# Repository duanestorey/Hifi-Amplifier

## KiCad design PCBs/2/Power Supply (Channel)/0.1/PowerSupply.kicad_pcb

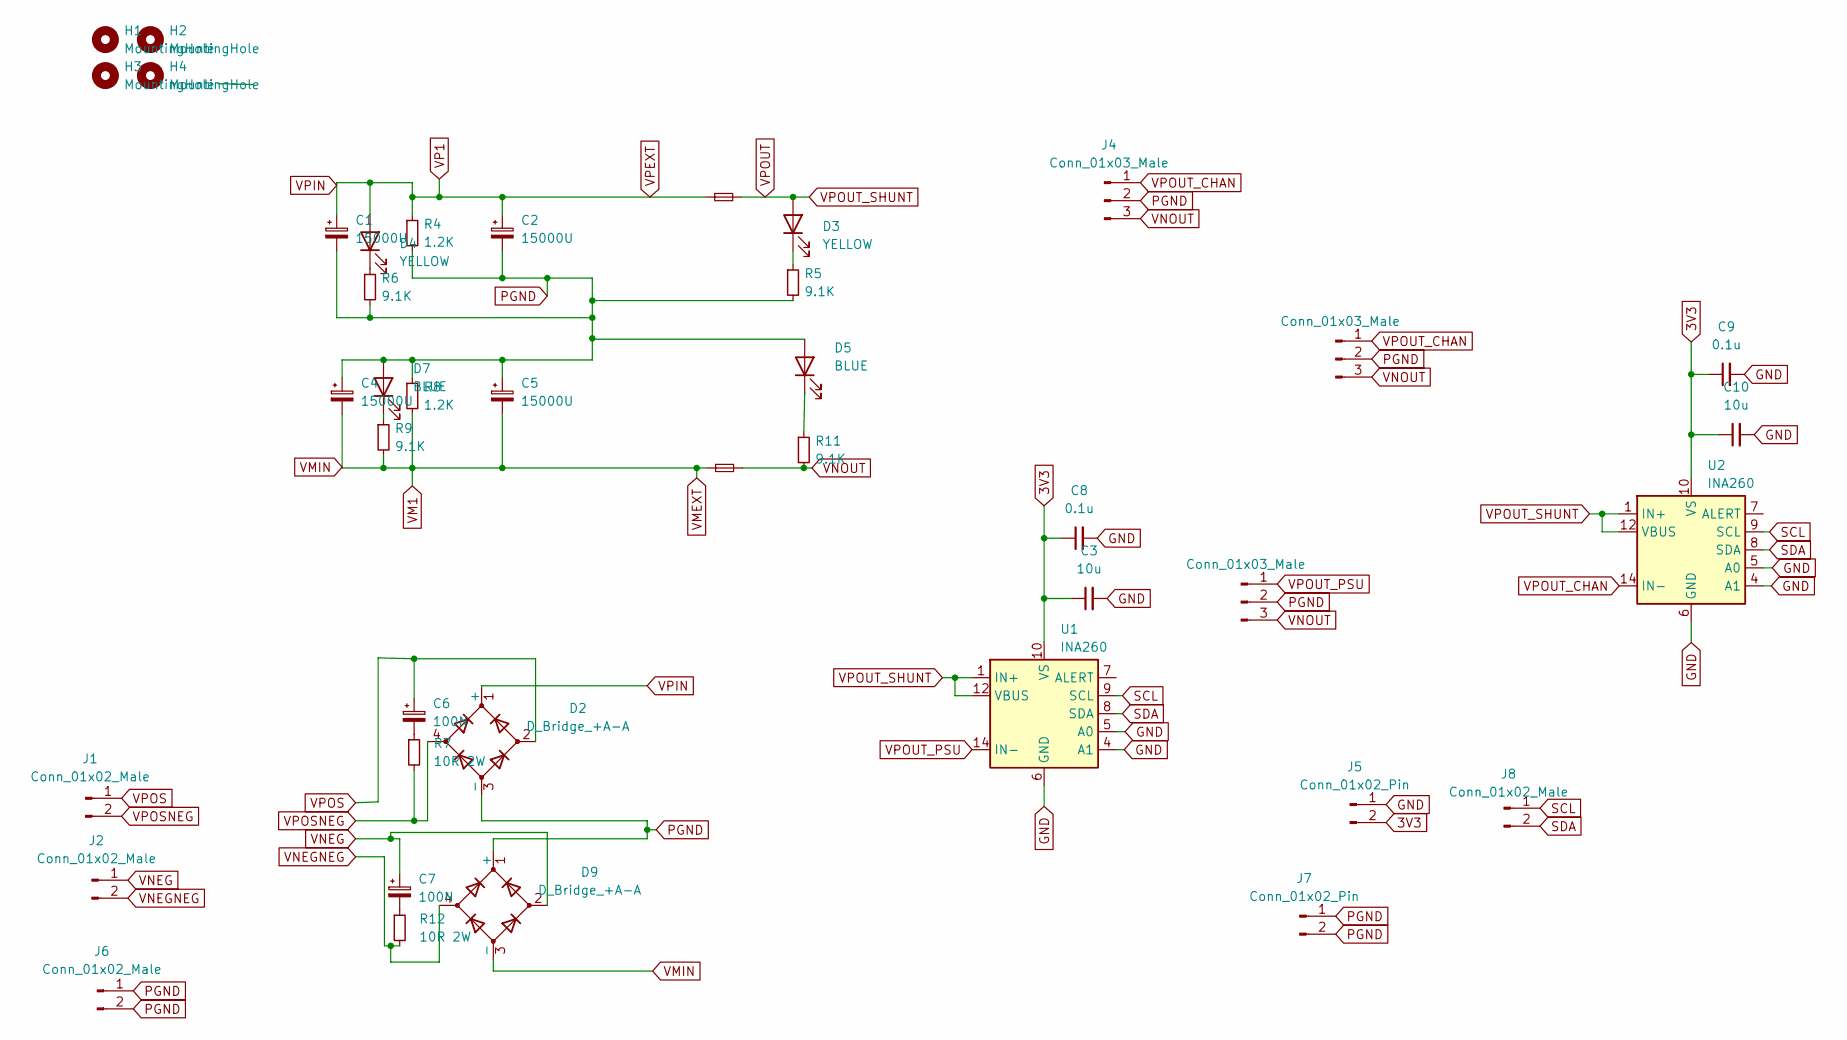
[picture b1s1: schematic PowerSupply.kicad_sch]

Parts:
C1, C2, C4, C5: 15000U; CP_Radial_D30.0mm_P10.00mm_SnapIn
C3, C10: 10u; C_1206_3216Metric_Pad1.33x1.80mm_HandSolder
C6, C7: 100N; C_Rect_L13.0mm_W6.0mm_P10.00mm_FKS3_FKP3_MKS4
C8, C9: 0.1u; C_0805_2012Metric_Pad1.18x1.45mm_HandSolder
D2, D9: D_Bridge_+A-A; Diode_Bridge_Vishay_DFS
D3, D4: YELLOW; LED_0805_2012Metric_Pad1.15x1.40mm_HandSolder
D5, D7: BLUE; LED_0805_2012Metric_Pad1.15x1.40mm_HandSolder
F1, F2: Fuse_Small; Aliexpress Fuse 5x20
H1, H3: MountingHole; MountingHole_3mm
H2, H4: MountingHole; MountingHole_3.2mm_M3
J1, J2, J6: Conn_01x02_Male; JST_VH_B2P-VH-B_1x02_P3.96mm_Vertical
J3, J4, J10: Conn_01x03_Male; JST_VH_B3P-VH_1x03_P3.96mm_Vertical
J5, J7: Conn_01x02_Pin; JST_PH_B2B-PH-K_1x02_P2.00mm_Vertical
J8: Conn_01x02_Male; JST_PH_B2B-PH-K_1x02_P2.00mm_Vertical
R4, R8: 1.2K; R_Axial_DIN0414_L11.9mm_D4.5mm_P15.24mm_Horizontal
R5, R6, R9, R11: 9.1K; R_0805_2012Metric_Pad1.20x1.40mm_HandSolder
R7, R12: 10R 2W; R_Axial_DIN0411_L9.9mm_D3.6mm_P15.24mm_Horizontal
U1, U2: INA260; TSSOP-16_4.4x5mm_P0.65mm

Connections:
3V3: C3.1, C8.1, C9.1, C10.1, J5.2, U1.10 (VS), U2.10 (VS)
GND: C3.2, C8.2, C9.2, C10.2, J5.1, U1.4 (A1), U1.5 (A0), U1.6 (GND), U1.11 (GND), U2.4 (A1), U2.5 (A0), U2.6 (GND), U2.11 (GND)
unnamed: C6.2, R7.1
unnamed: C7.2, R12.1
unnamed: D3.1 (K), R5.1
unnamed: D4.1 (K), R6.1
unnamed: D5.1 (K), R11.1
unnamed: D7.1 (K), R9.1
PGND: C1.2, C2.2, C4.1, C5.1, D2.3 (-), D5.2 (A), D7.2 (A), D9.1 (+), J3.2, J4.2, J6.1, J6.2, J7.1, J7.2, J10.2, R4.2, R5.2, R6.2, R8.1
SCL: J8.1, U1.9 (SCL), U2.9 (SCL)
SDA: J8.2, U1.8 (SDA), U2.8 (SDA)
VM1: C4.2, C5.2, D9.3 (-), F2.1, R8.2, R9.2
VNEG: C7.1, D9.2, J2.1
VNEGNEG: D9.4, J2.2, R12.2
VNOUT: F2.2, J3.3, J4.3, J10.3, R11.2
VP1: C1.1, C2.1, D2.1 (+), D4.2 (A), F1.1, R4.1
VPOS: C6.1, D2.2, J1.1
VPOSNEG: D2.4, J1.2, R7.2
VPOUT: D3.2 (A), F1.2, U1.1 (IN+), U1.2 (IN+), U1.3 (IN+), U1.12 (VBUS), U2.1 (IN+), U2.2 (IN+), U2.3 (IN+), U2.12 (VBUS)
VPOUT_CHAN: J4.1, J10.1, U2.14 (IN-), U2.15 (IN-), U2.16 (IN-)
VPOUT_PSU: J3.1, U1.14 (IN-), U1.15 (IN-), U1.16 (IN-)

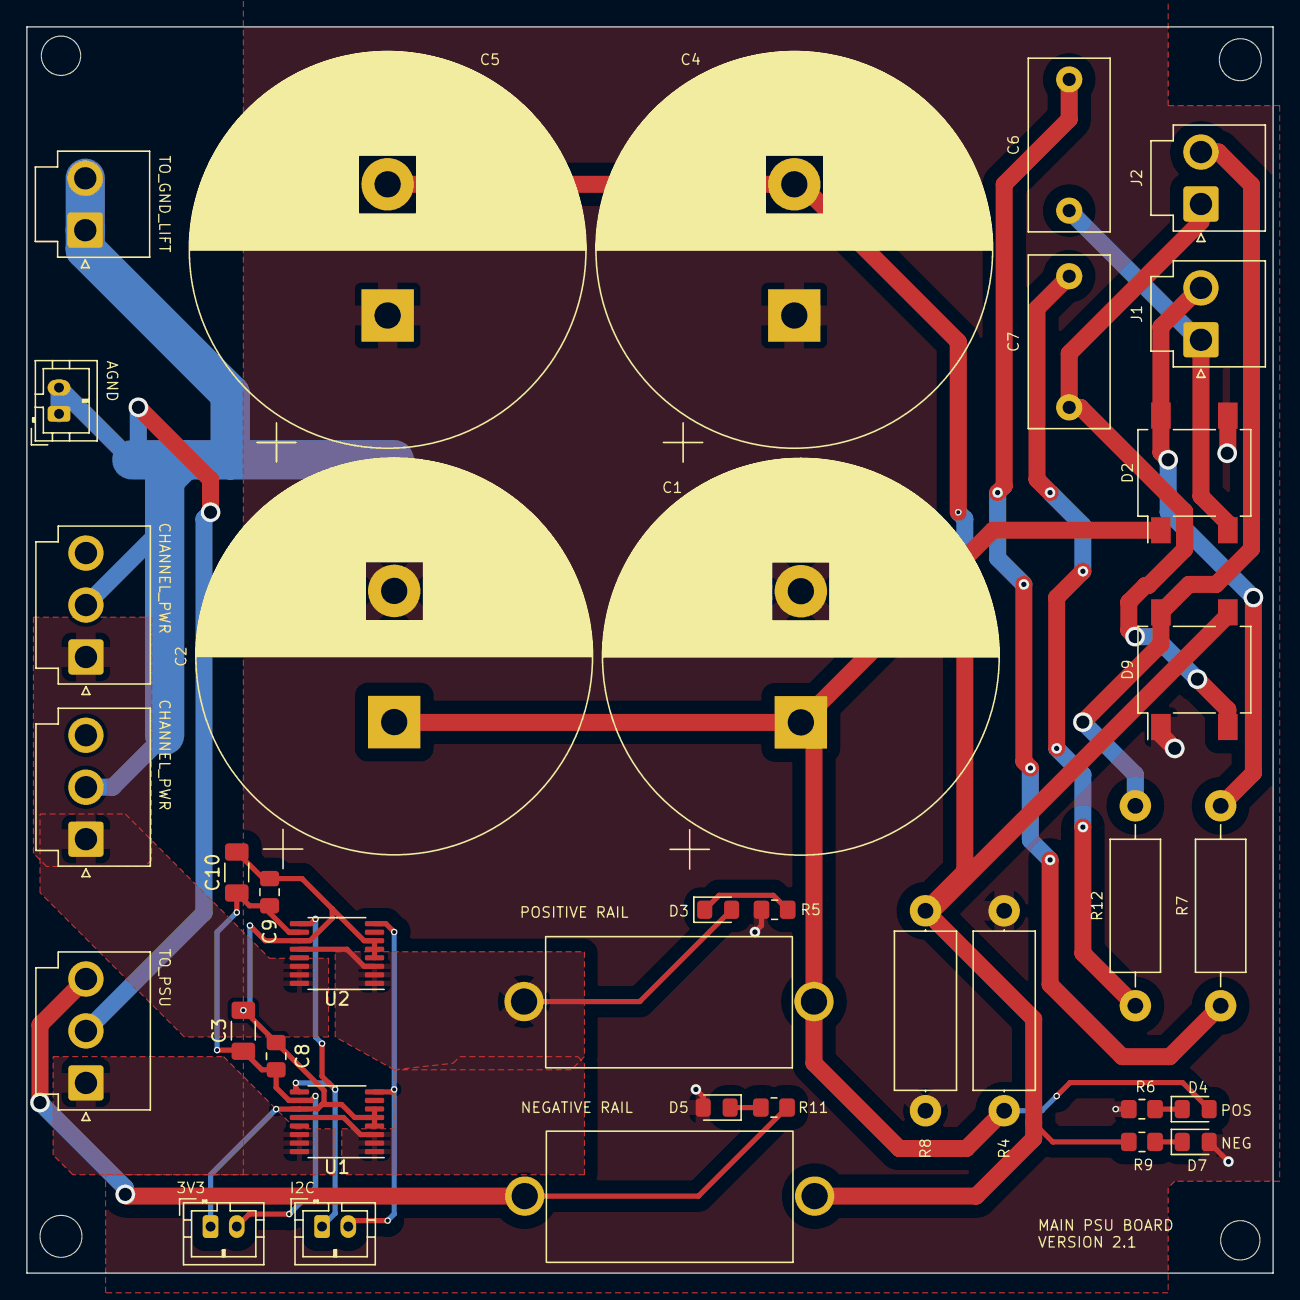
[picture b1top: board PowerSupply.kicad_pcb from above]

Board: 2 copper layers, 95.0 x 95.0 mm, 41 parts (0 on the bottom side), 21 nets.

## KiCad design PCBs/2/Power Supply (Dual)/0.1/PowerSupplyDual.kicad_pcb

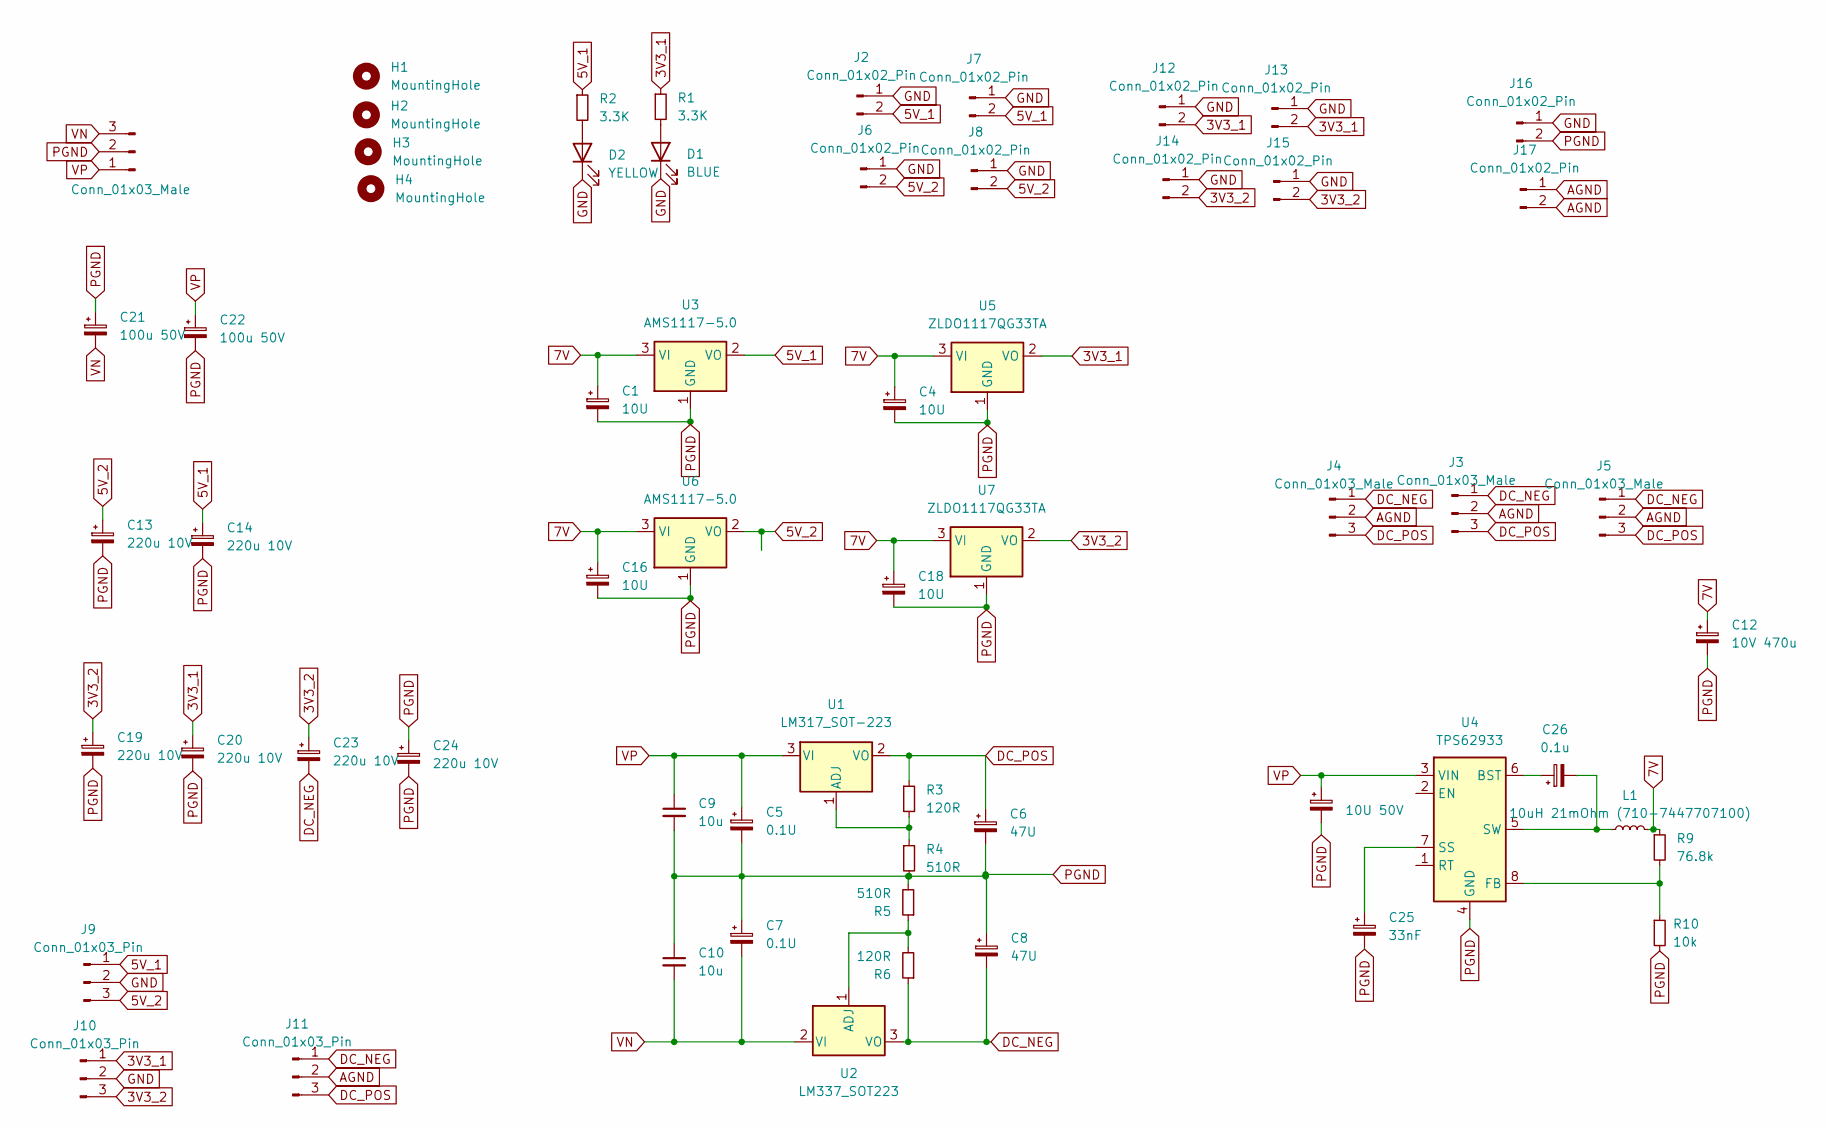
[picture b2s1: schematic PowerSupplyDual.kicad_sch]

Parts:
C1, C4, C16, C18: 10U; C_1206_3216Metric_Pad1.33x1.80mm_HandSolder
C5, C7: 0.1U; C_0603_1608Metric_Pad1.08x0.95mm_HandSolder
C6, C8: 47U; C_1206_3216Metric_Pad1.33x1.80mm_HandSolder
C9, C10: 10u; C_1206_3216Metric_Pad1.33x1.80mm_HandSolder
C11: 10U 50V; C_1206_3216Metric_Pad1.33x1.80mm_HandSolder
C12: 10V 470u; CP_Radial_D8.0mm_P3.50mm
C13, C14, C19, C20, C23, C24: 220u 10V; CP_Radial_D6.3mm_P2.50mm
C21, C22: 100u 50V; CP_Radial_D8.0mm_P3.50mm
C25: 33nF; C_1206_3216Metric_Pad1.33x1.80mm_HandSolder
C26: 0.1u; C_0805_2012Metric_Pad1.18x1.45mm_HandSolder
D1: BLUE; LED_0805_2012Metric_Pad1.15x1.40mm_HandSolder
D2: YELLOW; LED_0805_2012Metric_Pad1.15x1.40mm_HandSolder
H1, H2, H3, H4: MountingHole; MountingHole_3.2mm_M3
J1: Conn_01x03_Male; JST_VH_B3P-VH_1x03_P3.96mm_Vertical
J2, J6, J7, J8, J12, J13, J14, J15, J17: Conn_01x02_Pin; JST_PH_B2B-PH-K_1x02_P2.00mm_Vertical
J3, J4, J5: Conn_01x03_Male; JST_PH_B3B-PH-K_1x03_P2.00mm_Vertical
J9, J10, J11: Conn_01x03_Pin; PinHeader_1x03_P2.54mm_Vertical
J16: Conn_01x02_Pin; PinHeader_1x02_P2.54mm_Vertical
L1: 10uH 21mOhm (710-7447707100); L_Bourns_SRR1208_12.7x12.7mm
R1, R2: 3.3K; R_0603_1608Metric_Pad0.98x0.95mm_HandSolder
R3, R6: 120R; R_0603_1608Metric_Pad0.98x0.95mm_HandSolder
R4, R5: 510R; R_0603_1608Metric_Pad0.98x0.95mm_HandSolder
R9: 76.8k; R_0603_1608Metric_Pad0.98x0.95mm_HandSolder
R10: 10k; R_0603_1608Metric_Pad0.98x0.95mm_HandSolder
U1: LM317_SOT-223; SOT-223-3_TabPin2
U2: LM337_SOT223; SOT-223-3_TabPin2
U3, U6: AMS1117-5.0; SOT-223-3_TabPin2
U4: TPS62933; SOT-583-8
U5, U7: ZLDO1117QG33TA; SOT-223-3_TabPin2

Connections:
3V3_1: C20.1, J10.1, J12.2, J13.2, R1.1, U5.2 (VO)
3V3_2: C19.1, C23.1, J10.3, J14.2, J15.2, U7.2 (VO)
5V_1: C14.1, J2.2, J7.2, J9.1, R2.1, U3.2 (VO)
5V_2: C13.1, J6.2, J8.2, J9.3, U6.2 (VO)
7V: C1.1, C4.1, C12.1, C16.1, C18.1, L1.2, R9.1, U3.3 (VI), U5.3 (VI), U6.3 (VI), U7.3 (VI)
AGND: J3.2, J4.2, J5.2, J11.2, J17.1, J17.2
DC_NEG: C8.2, C23.2, J3.1, J4.1, J5.1, J11.1, R6.1, U2.3 (VO)
DC_POS: C6.1, J3.3, J4.3, J5.3, J11.3, R3.1, U1.2 (VO)
GND: D1.1 (K), D2.1 (K), J2.1, J6.1, J7.1, J8.1, J9.2, J10.2, J12.1, J13.1, J14.1, J15.1, J16.1
unnamed: D1.2 (A), R1.2
unnamed: D2.2 (A), R2.2
unnamed: R3.2, R4.1, U1.1 (ADJ)
unnamed: R5.1, R6.2, U2.1 (ADJ)
unnamed: C26.1, U4.6 (BST)
unnamed: R9.2, R10.1, U4.8 (FB)
unnamed: C25.1, U4.7 (SS)
unnamed: C26.2, L1.1, U4.5 (SW)
PGND: C1.2, C4.2, C5.2, C6.2, C7.1, C8.1, C9.2, C10.1, C11.2, C12.2, C13.2, C14.2, C16.2, C18.2, C19.2, C20.2, C21.1, C22.2, C24.1, C24.2, C25.2, J1.2, J16.2, R4.2, R5.2, R10.2, U3.1 (GND), U4.4 (GND), U5.1 (GND), U6.1 (GND), U7.1 (GND)
VN: C7.2, C10.2, C21.2, J1.3, U2.2 (VI)
VP: C5.1, C9.1, C11.1, C22.1, J1.1, U1.3 (VI), U4.3 (VIN)

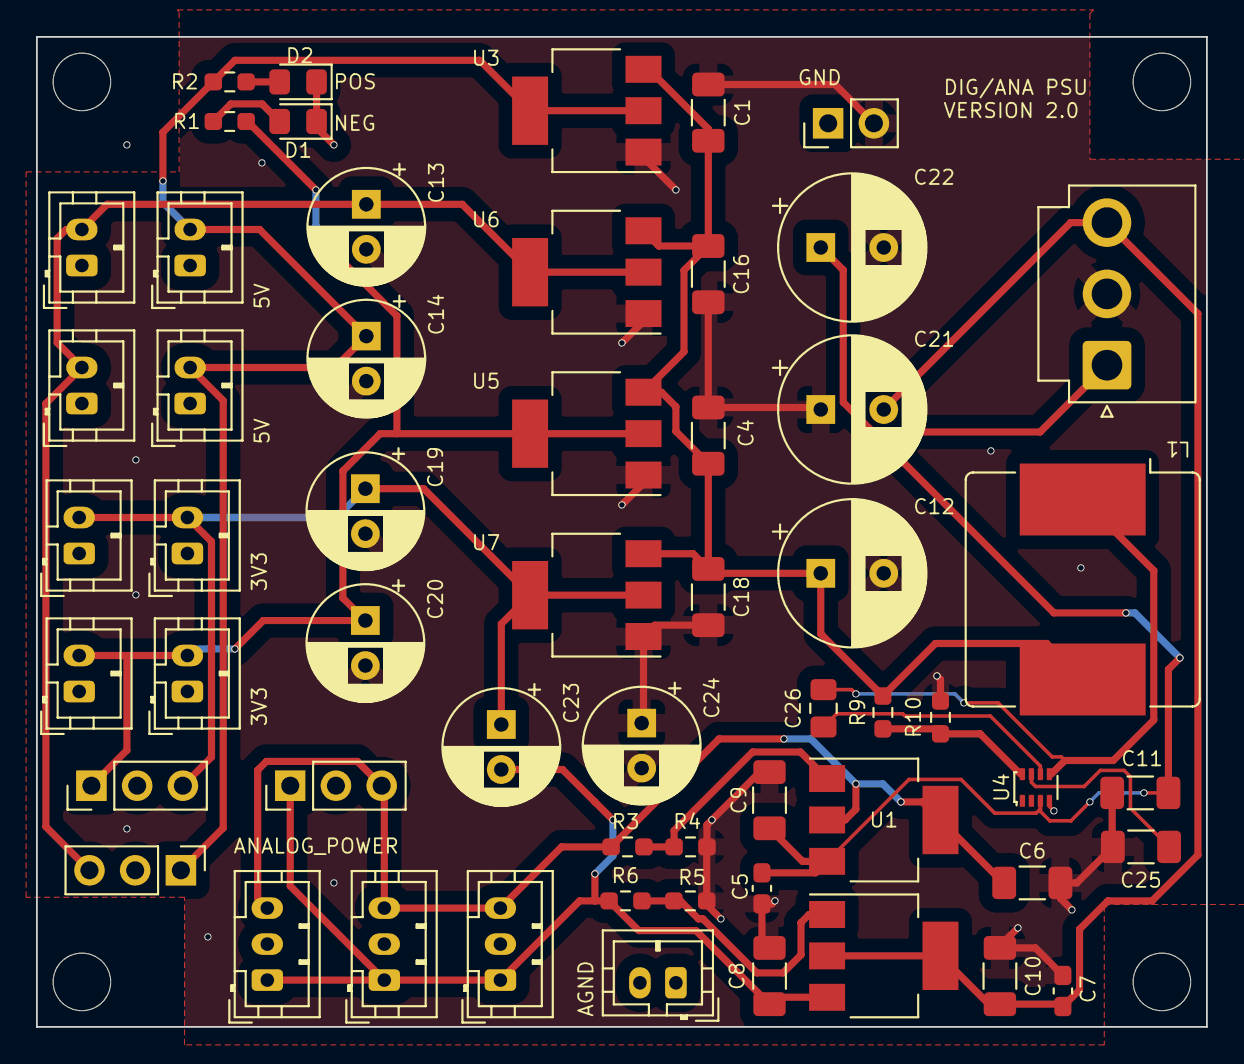
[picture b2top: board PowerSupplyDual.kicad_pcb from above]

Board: 4 copper layers, 65.0 x 55.0 mm, 61 parts (0 on the bottom side), 20 nets.

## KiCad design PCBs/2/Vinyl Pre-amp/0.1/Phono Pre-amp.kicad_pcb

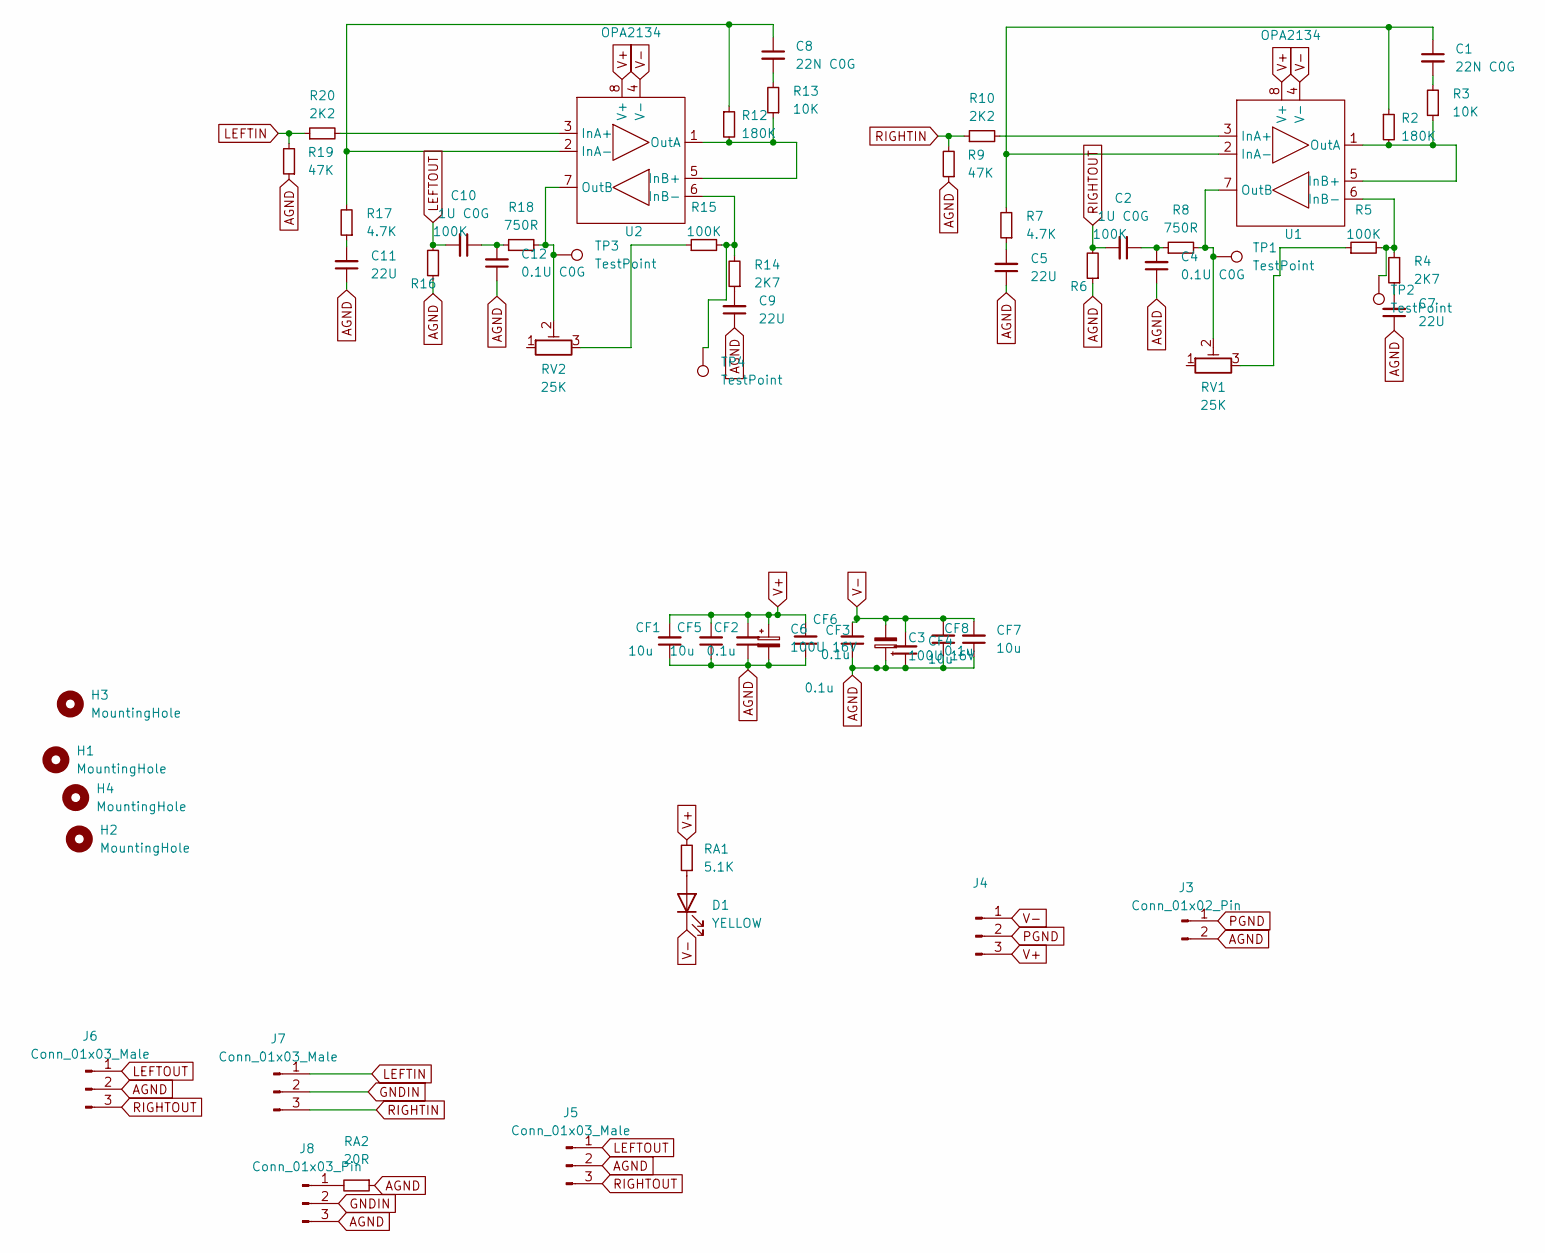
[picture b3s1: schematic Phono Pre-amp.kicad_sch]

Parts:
C1, C8: 22N C0G; C_0805_2012Metric_Pad1.18x1.45mm_HandSolder
C2, C10: 1U C0G; CP_Radial_D5.0mm_P2.00mm
C3, C6: 100U 16V; CP_Radial_D6.3mm_P2.50mm
C4, C12: 0.1U C0G; C_1206_3216Metric_Pad1.33x1.80mm_HandSolder
C5, C7, C9, C11: 22U; CP_Radial_D6.3mm_P2.50mm
CF1, CF4, CF5, CF7: 10u; C_1206_3216Metric_Pad1.33x1.80mm_HandSolder
CF2, CF3, CF6, CF8: 0.1u; C_0805_2012Metric_Pad1.18x1.45mm_HandSolder
D1: YELLOW; LED_0805_2012Metric_Pad1.15x1.40mm_HandSolder
H1, H2, H3, H4: MountingHole; MountingHole_3.2mm_M3
J3: Conn_01x02_Pin; PinHeader_1x02_P2.54mm_Vertical
J4, J6, J7: Conn_01x03_Male; JST_PH_B3B-PH-K_1x03_P2.00mm_Vertical
J5: Conn_01x03_Male; PinHeader_1x03_P2.54mm_Vertical
J8: Conn_01x03_Pin; PinHeader_1x03_P2.54mm_Vertical
R2, R12: 180K; R_0805_2012Metric_Pad1.20x1.40mm_HandSolder
R3, R13: 10K; R_0805_2012Metric_Pad1.20x1.40mm_HandSolder
R4, R14: 2K7; R_0805_2012Metric_Pad1.20x1.40mm_HandSolder
R5, R6, R15, R16: 100K; R_0805_2012Metric_Pad1.20x1.40mm_HandSolder
R7, R17: 4.7K; R_0805_2012Metric_Pad1.20x1.40mm_HandSolder
R8, R18: 750R; R_0805_2012Metric_Pad1.20x1.40mm_HandSolder
R9, R19: 47K; R_0805_2012Metric_Pad1.20x1.40mm_HandSolder
R10, R20: 2K2; R_0805_2012Metric_Pad1.20x1.40mm_HandSolder
RA1: 5.1K; R_0603_1608Metric
RA2: 20R; R_0603_1608Metric
RV1, RV2: 25K; Potentiometer_Bourns_3296W_Vertical
TP1, TP2, TP3, TP4: TestPoint; TestPoint_THTPad_1.5x1.5mm_Drill0.7mm
U1, U2: OPA2134; DIP-8_W7.62mm_Socket

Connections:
AGND: C3.1, C4.1, C5.1, C6.2, C7.1, C9.1, C11.1, C12.1, CF1.1, CF2.1, CF3.1, CF4.1, CF5.1, CF6.1, CF7.1, CF8.1, J3.2, J5.2, J6.2, J8.3, R6.1, R9.1, R16.1, R19.1, RA2.1
GNDIN: J7.2, J8.2
LEFTIN: J7.1, R19.2, R20.1
LEFTOUT: C10.2, J5.1, J6.1, R16.2
unnamed: C1.2, R3.2
unnamed: C2.1, C4.2, R8.1
unnamed: C5.2, R7.1
unnamed: C7.2, R4.1
unnamed: C8.2, R13.2
unnamed: C9.2, R14.1
unnamed: C10.1, C12.2, R18.1
unnamed: C11.2, R17.1
unnamed: D1.2 (A), RA1.1
unnamed: J8.1, RA2.2
unnamed: R5.1, RV1.3
unnamed: R15.1, RV2.3
unnamed: R10.2, U1.3 (InA+)
unnamed: C1.1, R2.1, R7.2, U1.2 (InA-)
unnamed: R2.2, R3.1, U1.1 (OutA), U1.5 (InB+)
unnamed: R4.2, R5.2, TP2.1, U1.6 (InB-)
unnamed: R8.2, RV1.2, TP1.1, U1.7 (OutB)
unnamed: R20.2, U2.3 (InA+)
unnamed: C8.1, R12.1, R17.2, U2.2 (InA-)
unnamed: R12.2, R13.1, U2.1 (OutA), U2.5 (InB+)
unnamed: R14.2, R15.2, TP4.1, U2.6 (InB-)
unnamed: R18.2, RV2.2, TP3.1, U2.7 (OutB)
PGND: J3.1, J4.2
RIGHTIN: J7.3, R9.2, R10.1
RIGHTOUT: C2.2, J5.3, J6.3, R6.2
V+: C6.1, CF1.2, CF2.2, CF5.2, CF6.2, J4.3, RA1.2, U1.8 (V+), U2.8 (V+)
V-: C3.2, CF3.2, CF4.2, CF7.2, CF8.2, D1.1 (K), J4.1, U1.4 (V-), U2.4 (V-)

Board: 2 copper layers, 59 parts (0 on the bottom side), 31 nets, no tracks yet.

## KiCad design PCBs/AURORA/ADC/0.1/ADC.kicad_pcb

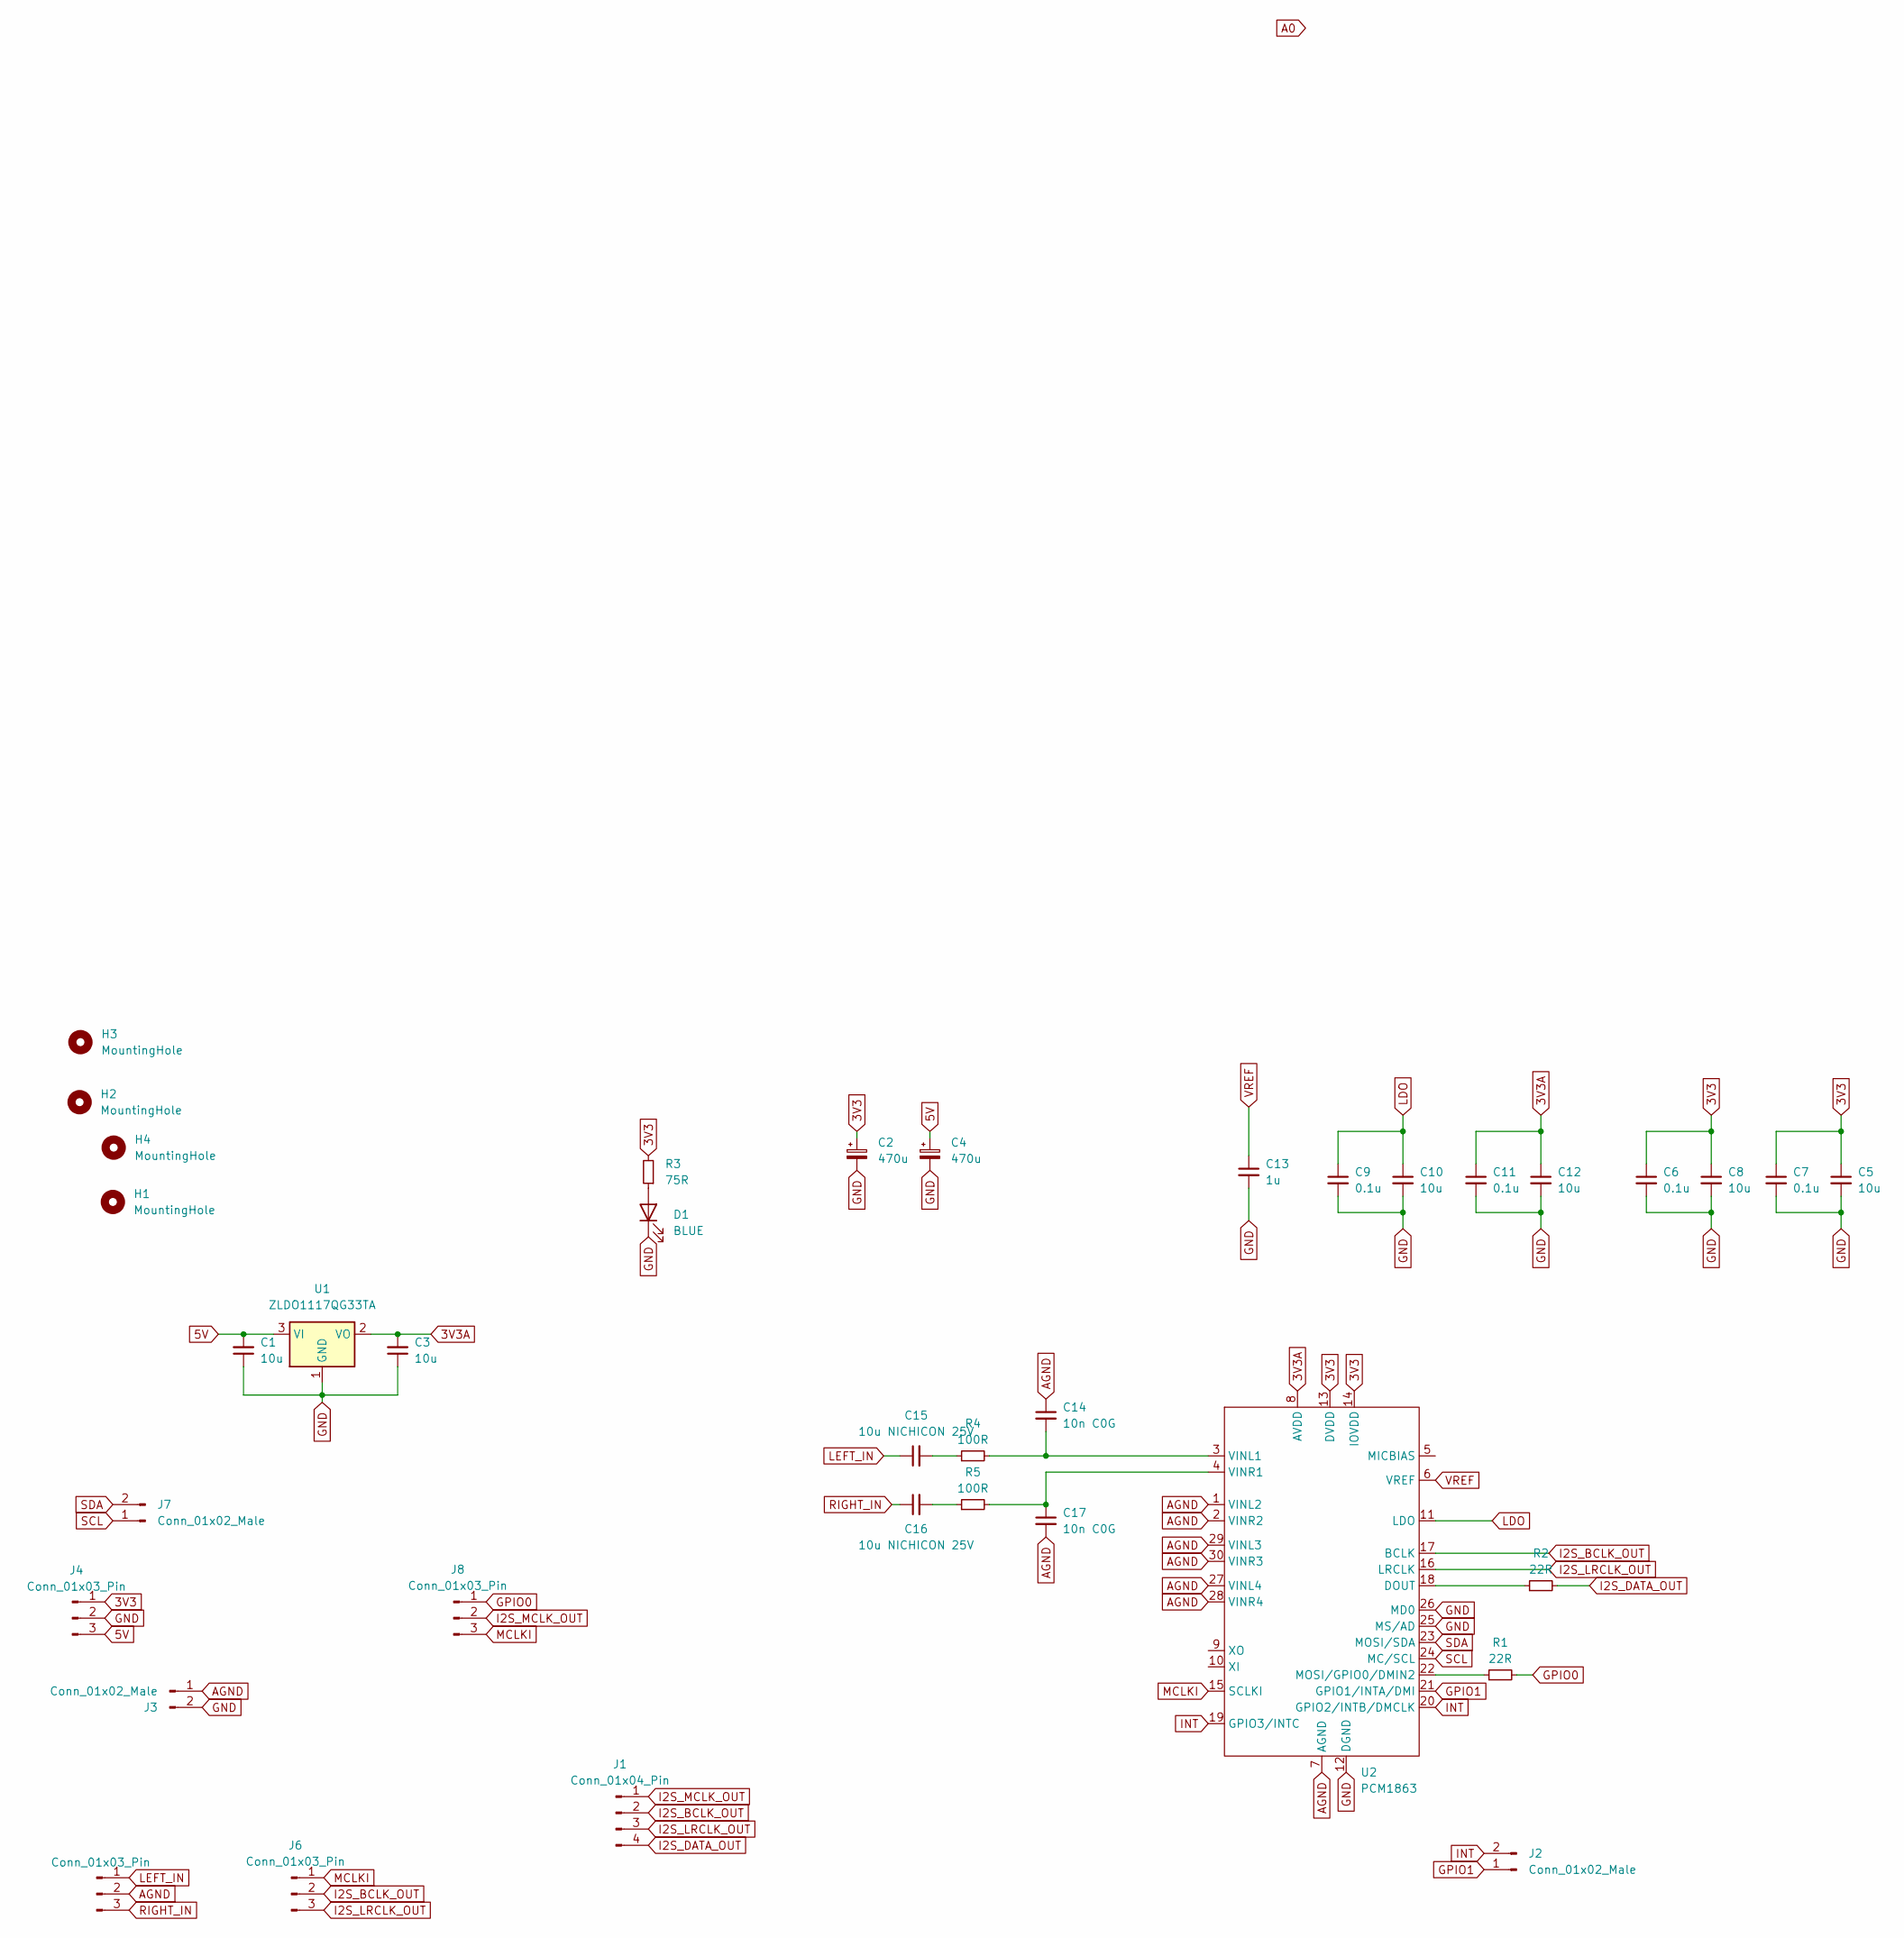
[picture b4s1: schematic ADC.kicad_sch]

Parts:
C1, C3, C5, C8, C10, C12: 10u; C_1206_3216Metric_Pad1.33x1.80mm_HandSolder
C2, C4: 470u; CP_Radial_D6.3mm_P2.50mm
C6, C7, C9, C11: 0.1u; C_0805_2012Metric_Pad1.18x1.45mm_HandSolder
C13: 1u; C_1206_3216Metric_Pad1.33x1.80mm_HandSolder
C14, C17: 10n C0G; C_0805_2012Metric_Pad1.18x1.45mm_HandSolder; Mouser 791-0805N103G250CT
C15, C16: 10u NICHICON 25V; CP_Radial_D5.0mm_P2.00mm
D1: BLUE; LED_0805_2012Metric
H1, H2, H3, H4: MountingHole; MountingHole_3.2mm_M3_DIN965_Pad_TopOnly
J1: Conn_01x04_Pin; JST_PH_B4B-PH-K_1x04_P2.00mm_Vertical
J2, J7: Conn_01x02_Male; JST_PH_B2B-PH-K_1x02_P2.00mm_Vertical
J3: Conn_01x02_Male; PinHeader_1x02_P2.54mm_Vertical
J4, J5, J6: Conn_01x03_Pin; JST_PH_B3B-PH-K_1x03_P2.00mm_Vertical
J8: Conn_01x03_Pin; PinHeader_1x03_P2.54mm_Vertical
R1, R2: 22R; R_0805_2012Metric_Pad1.20x1.40mm_HandSolder; Mouser 603-RT0805FRE0722RL
R3: 75R; R_0603_1608Metric_Pad0.98x0.95mm_HandSolder
R4, R5: 100R; R_0805_2012Metric_Pad1.20x1.40mm_HandSolder; Mouser 603-RT0805FRE13100RL
U1: ZLDO1117QG33TA; SOT-223-3_TabPin2
U2: PCM1863; TSSOP-30_4.4x7.8mm_P0.5mm; Mouser 595-PCM1863DBT
U3: (no value)

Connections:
3V3: C2.1, C5.1, C6.1, C7.1, C8.1, J4.1, R3.2, U2.13 (DVDD), U2.14 (IOVDD)
3V3A: C3.2, C11.1, C12.1, U1.2 (VO), U2.8 (AVDD)
5V: C1.2, C4.1, J4.3, U1.3 (VI)
AGND: C14.1, C17.2, J3.1, J5.2, U2.1 (VINL2), U2.2 (VINR2), U2.7 (AGND), U2.27 (VINL4), U2.28 (VINR4), U2.29 (VINL3), U2.30 (VINR3)
GND: C1.1, C2.2, C3.1, C4.2, C5.2, C6.2, C7.2, C8.2, C9.2, C10.2, C11.2, C12.2, C13.2, D1.1 (K), J3.2, J4.2, U1.1 (GND), U2.12 (DGND), U2.25 (MS/AD), U2.26 (MD0)
GPIO0: J8.1, R1.2
GPIO1: J2.1, U2.21 (GPIO1/INTA/DMI)
I2S_BCLK_OUT: J1.2, J6.2, U2.17 (BCLK)
I2S_DATA_OUT: J1.4, R2.2
I2S_LRCLK_OUT: J1.3, J6.3, U2.16 (LRCLK)
I2S_MCLK_OUT: J1.1, J8.2
INT: J2.2, U2.19 (GPIO3/INTC), U2.20 (GPIO2/INTB/DMCLK)
LDO: C9.1, C10.1, U2.11 (LDO)
LEFT_IN: C15.1, J5.1
MCLKI: J6.1, J8.3, U2.15 (SCLKI)
unnamed: C15.2, R4.1
unnamed: C16.2, R5.1
unnamed: D1.2 (A), R3.1
unnamed: R2.1, U2.18 (DOUT)
unnamed: R1.1, U2.22 (MOSI/GPIO0/DMIN2)
unnamed: C14.2, R4.2, U2.3 (VINL1)
unnamed: C17.1, R5.2, U2.4 (VINR1)
RIGHT_IN: C16.1, J5.3
SCL: J7.1, U2.24 (MC/SCL)
SDA: J7.2, U2.23 (MOSI/SDA)
VREF: C13.1, U2.6 (VREF)

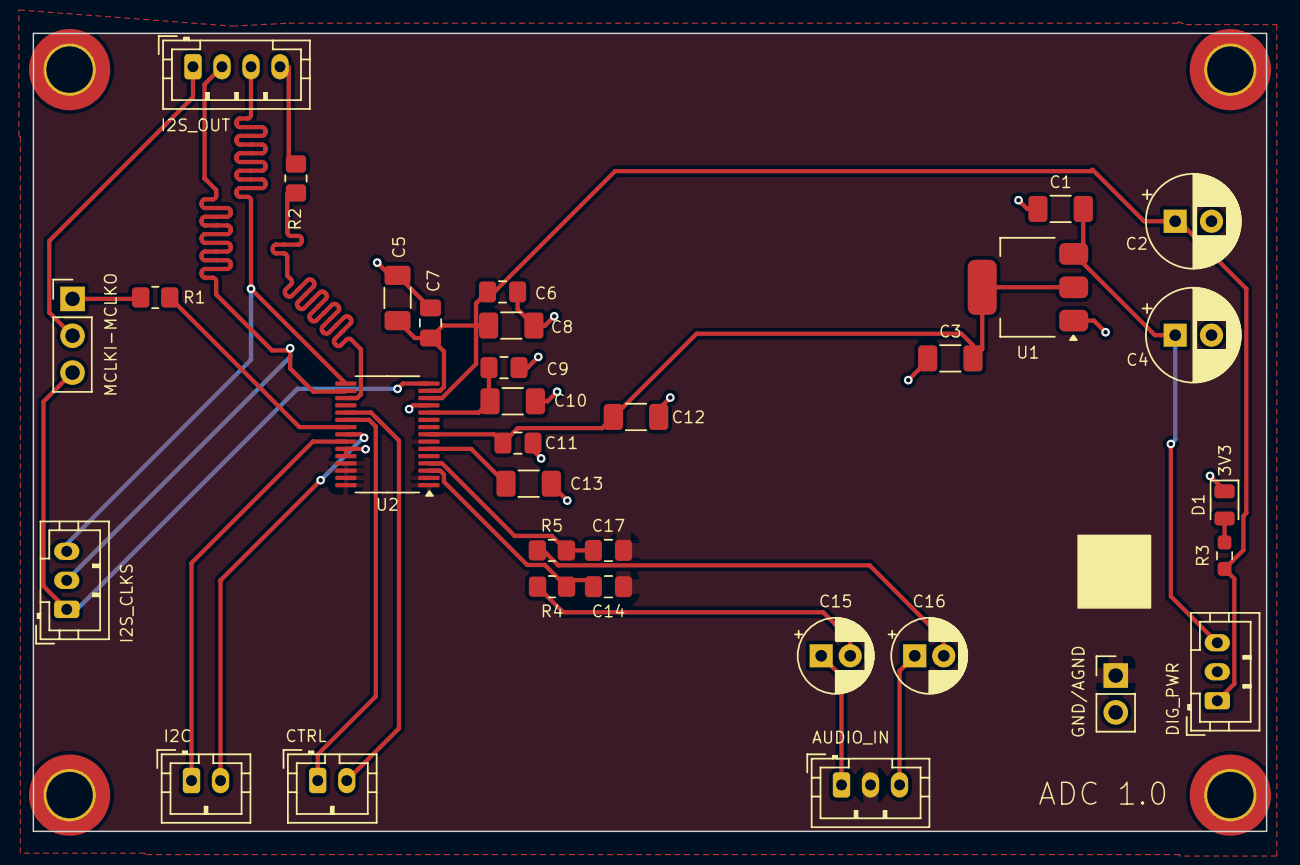
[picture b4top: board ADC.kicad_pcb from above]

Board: 2 copper layers, 85.0 x 55.0 mm, 37 parts (0 on the bottom side), 26 nets.
